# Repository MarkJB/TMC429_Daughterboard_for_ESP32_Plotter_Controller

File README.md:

# TMC429 Daughterboard for ESP32 Plotter Controller
 
Released under an MIT licence, no warranty implied or given, use at own risk etc etc.

This is an add-on (daughterboard) for the ESP32 Plotter Controller board (Rev A) to evaluate the TMC429 motion controller chip using the TMC429 Break-out-board.

Firmware TBD

[Schematic]( https://github.com/MarkJB/TMC429_Daughterboard_for_ESP32_Plotter_Controller/blob/master/schematic.pdf )

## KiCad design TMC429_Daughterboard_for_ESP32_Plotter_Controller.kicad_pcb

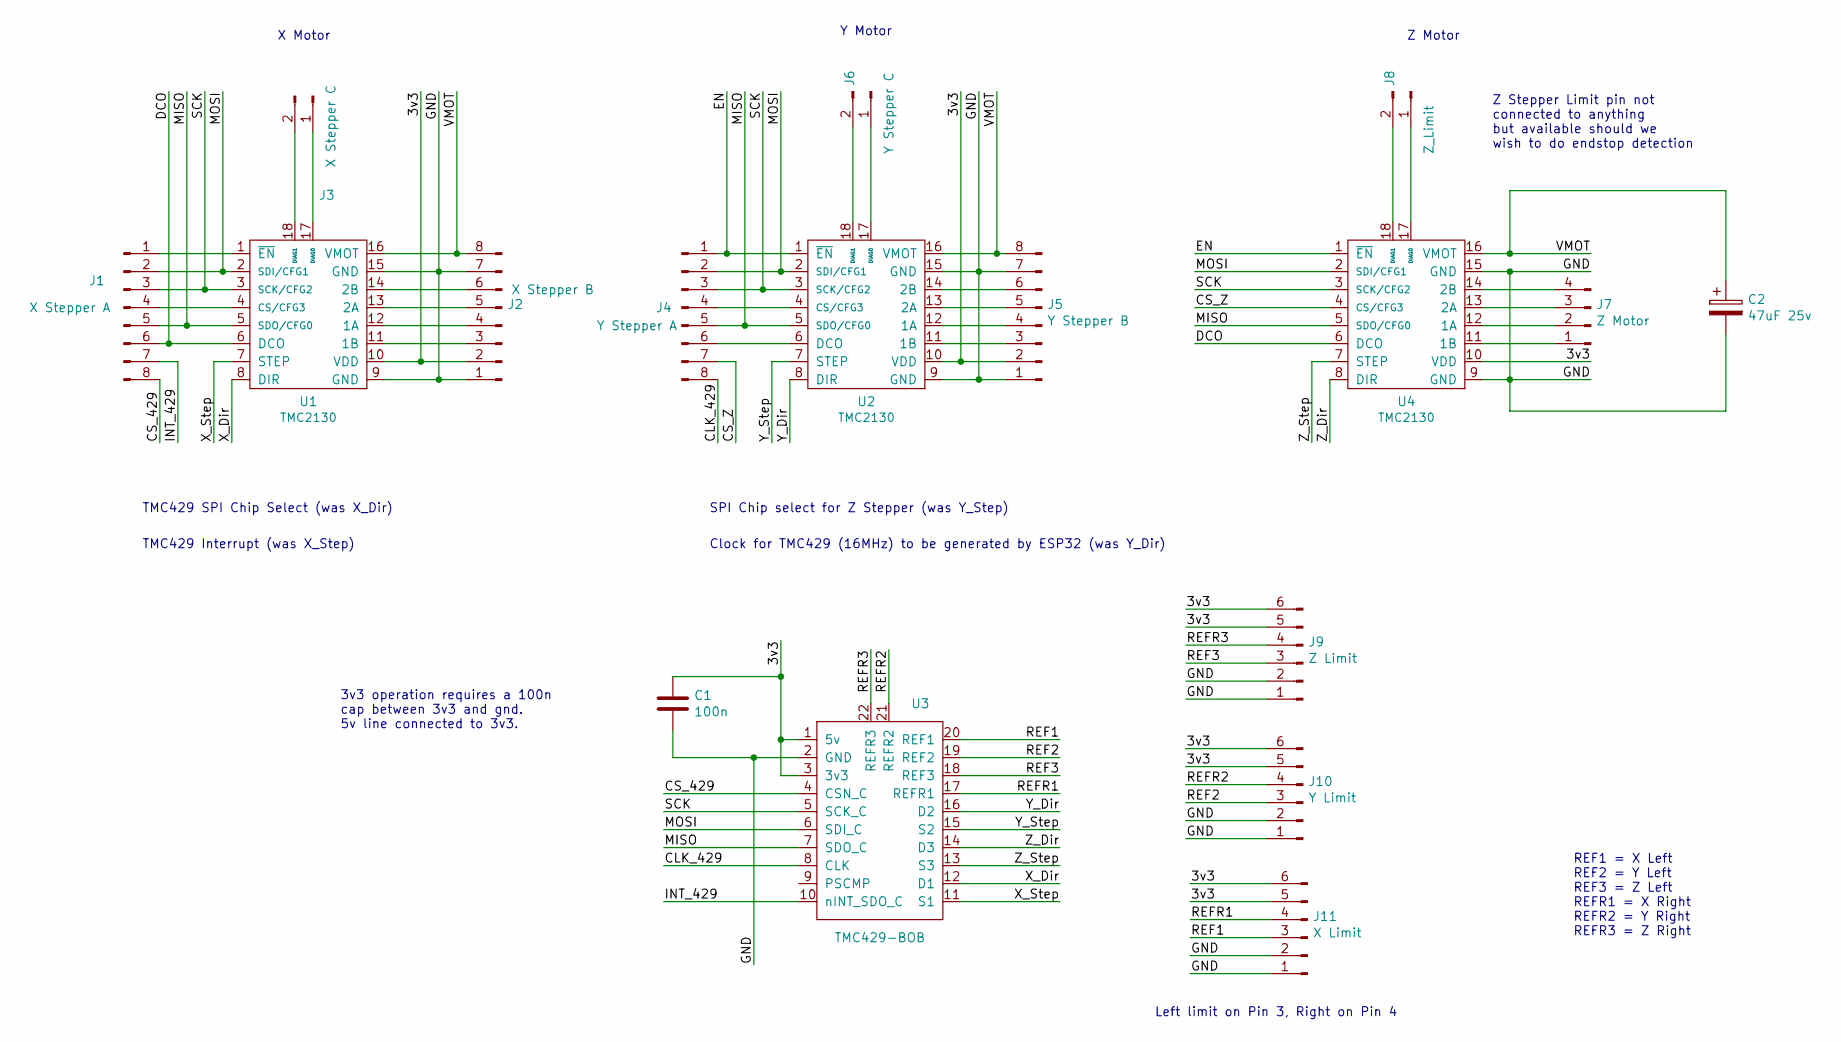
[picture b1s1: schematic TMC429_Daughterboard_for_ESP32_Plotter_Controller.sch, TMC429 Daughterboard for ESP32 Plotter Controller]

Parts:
C1: 100n; C_0805_2012Metric
C2: 47uF 25v; CP_Elec_6.3x5.4
J1: X Stepper A; PinHeader_1x08_P2.54mm_Vertical
J2: X Stepper B; PinHeader_1x08_P2.54mm_Vertical
J3: X Stepper C; PinHeader_1x02_P2.54mm_Vertical
J4: Y Stepper A; PinHeader_1x08_P2.54mm_Vertical
J5: Y Stepper B; PinHeader_1x08_P2.54mm_Vertical
J6: Y Stepper C; PinHeader_1x02_P2.54mm_Vertical
J7: Z Motor; PinHeader_1x04_P2.54mm_Horizontal
J8: Z_Limit; PinHeader_1x02_P2.54mm_Horizontal
J9: Z Limit; PinHeader_2x03_P2.54mm_Horizontal
J10: Y Limit; PinHeader_2x03_P2.54mm_Horizontal
J11: X Limit; PinHeader_2x03_P2.54mm_Horizontal
U1, U2, U4: TMC2130; StepstickTMCv2
U3: TMC429-BOB

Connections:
/3v3: C1.1, J2.2, J5.2, J9.5, J9.6, J10.5, J10.6, J11.5, J11.6, U1.10 (VDD), U2.10 (VDD), U3.1 (5v), U3.3 (3v3), U4.10 (VDD)
/CLK_429: J4.8, U3.8 (CLK)
/CS_429: J1.8, U3.4 (CSN_C)
/CS_Z: J4.7, U4.4 (CS/CFG3)
/DCO: J1.6, U1.6 (DCO), U4.6 (DCO)
/EN: J4.1, U2.1 (~EN), U4.1 (~EN)
/GND: C1.2, C2.2, J2.1, J2.7, J5.1, J5.7, J9.1, J9.2, J10.1, J10.2, J11.1, J11.2, U1.9 (GND), U1.15 (GND), U2.9 (GND), U2.15 (GND), U3.2 (GND), U4.9 (GND), U4.15 (GND)
/INT_429: J1.7, U3.10 (nINT_SDO_C)
/MISO: J1.5, J4.5, U1.5 (SDO/CFG0), U2.5 (SDO/CFG0), U3.7 (SDO_C), U4.5 (SDO/CFG0)
/MOSI: J1.2, J4.2, U1.2 (SDI/CFG1), U2.2 (SDI/CFG1), U3.6 (SDI_C), U4.2 (SDI/CFG1)
/REF1: J11.3, U3.20 (REF1)
/REF2: J10.3, U3.19 (REF2)
/REF3: J9.3, U3.18 (REF3)
/REFR1: J11.4, U3.17 (REFR1)
/REFR2: J10.4, U3.21 (REFR2)
/REFR3: J9.4, U3.22 (REFR3)
/SCK: J1.3, J4.3, U1.3 (SCK/CFG2), U2.3 (SCK/CFG2), U3.5 (SCK_C), U4.3 (SCK/CFG2)
/VMOT: C2.1, J2.8, J5.8, U1.16 (VMOT), U2.16 (VMOT), U4.16 (VMOT)
/X_Dir: U1.8 (DIR), U3.12 (D1)
/X_Step: U1.7 (STEP), U3.11 (S1)
/Y_Dir: U2.8 (DIR), U3.16 (D2)
/Y_Step: U2.7 (STEP), U3.15 (S2)
/Z_Dir: U3.14 (D3), U4.8 (DIR)
/Z_Step: U3.13 (S3), U4.7 (STEP)
unnamed: J1.1, U1.1 (~EN)
unnamed: J1.4, U1.4 (CS/CFG3)
unnamed: J2.3, U1.11 (1B)
unnamed: J2.4, U1.12 (1A)
unnamed: J2.5, U1.13 (2A)
unnamed: J2.6, U1.14 (2B)
unnamed: J3.1, U1.17 (DIAG0)
unnamed: J3.2, U1.18 (DIAG1)
unnamed: J4.4, U2.4 (CS/CFG3)
unnamed: J4.6, U2.6 (DCO)
unnamed: J5.3, U2.11 (1B)
unnamed: J5.4, U2.12 (1A)
unnamed: J5.5, U2.13 (2A)
unnamed: J5.6, U2.14 (2B)
unnamed: J6.1, U2.17 (DIAG0)
unnamed: J6.2, U2.18 (DIAG1)
unnamed: J7.1, U4.11 (1B)
unnamed: J7.2, U4.12 (1A)
unnamed: J7.3, U4.13 (2A)
unnamed: J7.4, U4.14 (2B)
unnamed: J8.1, U4.17 (DIAG0)
unnamed: J8.2, U4.18 (DIAG1)

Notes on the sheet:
X Motor
Y Motor
Left limit on Pin 3, Right on Pin 4
REF1 = X Left REF2 = Y Left REF3 = Z Left REFR1 = X Right REFR2 = Y Right REFR3 = Z Right
TMC429 SPI Chip Select (was X_Dir)
TMC429 Interrupt (was X_Step)
3v3 operation requires a 100n cap between 3v3 and gnd. 5v line connected to 3v3.
Z Motor
Clock for TMC429 (16MHz) to be generated by ESP32 (was Y_Dir)
SPI Chip select for Z Stepper (was Y_Step)
Z Stepper Limit pin not connected to anything but available should we wish to do endstop detection

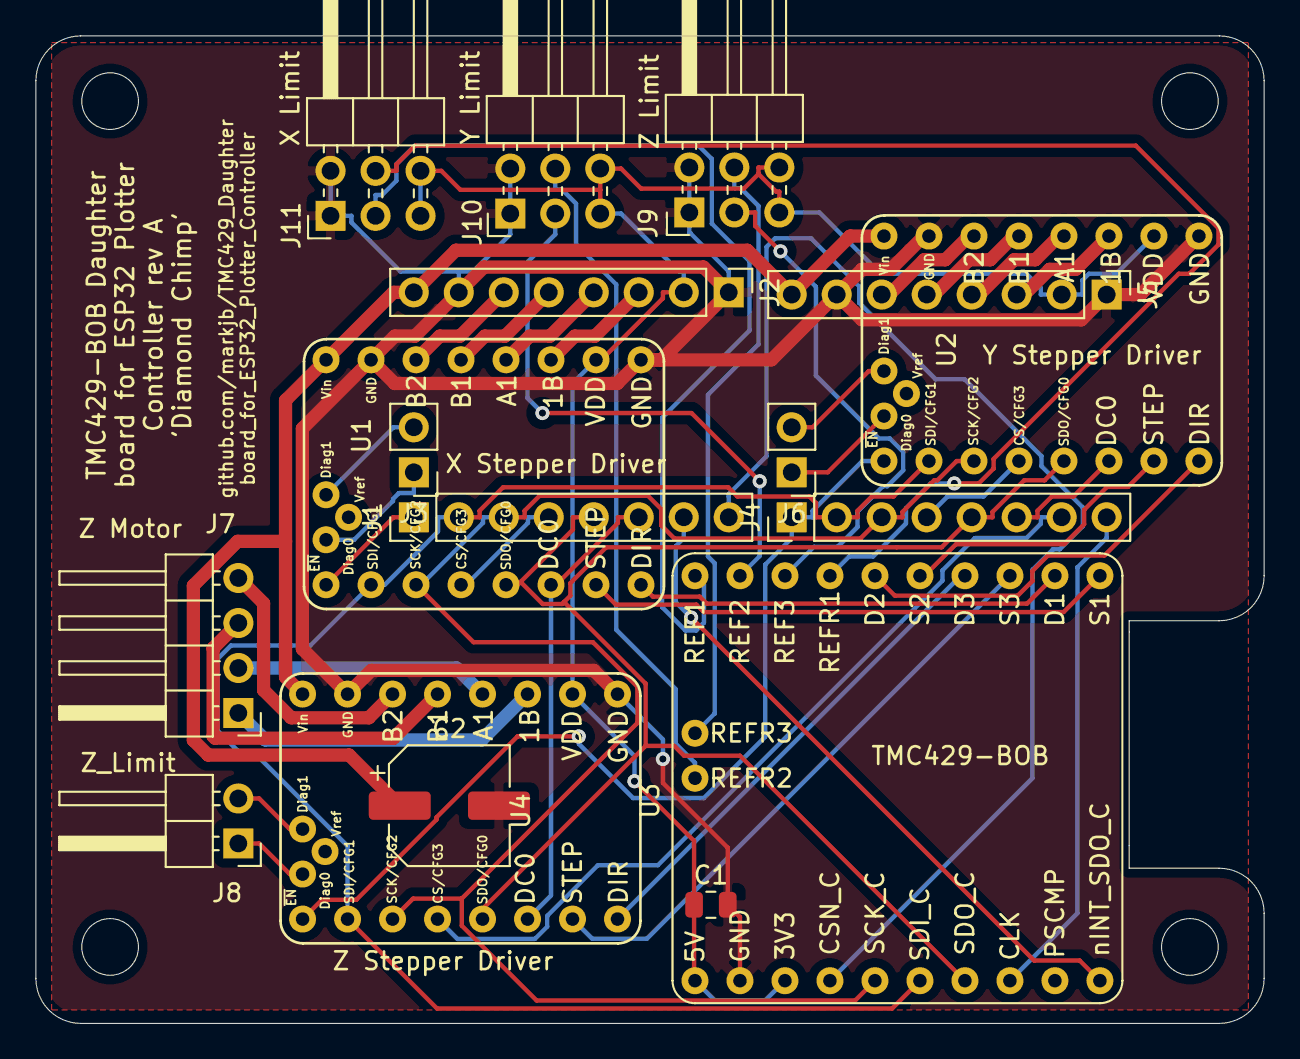
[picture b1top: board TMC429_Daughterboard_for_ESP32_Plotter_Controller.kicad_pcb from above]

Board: 2 copper layers, 69.3 x 55.8 mm, 21 parts (0 on the bottom side), 46 nets.

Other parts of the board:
H1, H2, H3, H4: MountingHole_3.2mm_M3

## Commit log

2021-03-03 Fix MISO/CS pins
    Moved MISO to correct pin and updated Schematic and PCB.
